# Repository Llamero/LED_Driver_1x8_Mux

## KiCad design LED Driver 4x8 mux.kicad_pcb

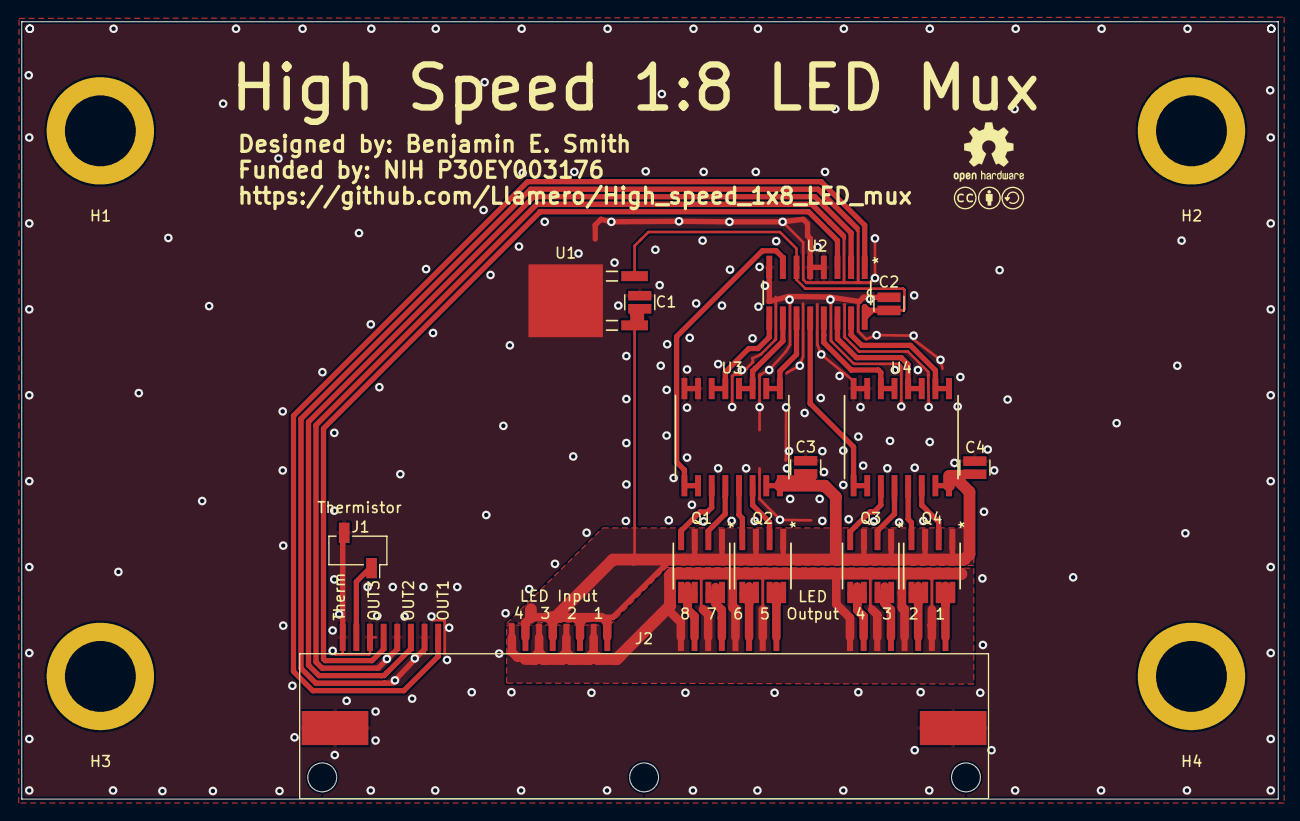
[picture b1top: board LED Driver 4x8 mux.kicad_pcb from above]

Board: 2 copper layers, 117.0 x 72.4 mm, 20 parts (0 on the bottom side), 32 nets.

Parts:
C1, C2, C3, C4: 2.2uF; 0508_Capacitor
H1, H2, H3, H4: MountingHole; 14-20_standoff
J1: 2 pin header; PinSocket_1x02_P2.54mm_Vertical_SMD_Pin1Right
J2: 8P8C_Shielded_x4; RJ45_x4-RJSSE-5380-04
LOGO1: CC license; Creative_commons_license
LOGO3: OSHW Logo; OSHW-Logo2_7.3x6mm_SilkScreen
Q1, Q2, Q3, Q4: SO8_IRF9358TRPBF_INF; IRF9358TRPBF-2x_p-channel
U1: NCV7805BDTRKG; 12V-5V_lin_reg_NCV7805BDTRKG
U2: SN74LV138AT_D_16; SN74LV138ATD
U3, U4: SOIC16-W_MC_MCH; TC4468EOE

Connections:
/+5V: C2.2, U1.3, U2.6, U2.16
/Gate1: Q4.2, U4.14
/Gate2: Q4.4, U4.13
/Gate3: Q3.2, U4.12
/Gate4: Q3.4, U4.11
/Gate5: Q2.2, U3.14
/Gate6: Q2.4, U3.13
/Gate7: Q1.2, U3.12
/Gate8: Q1.4, U3.11
/IN1: U2.15, U4.1, U4.2
/IN2: U2.14, U4.3, U4.4
/IN3: U2.13, U4.5, U4.6
/IN4: U2.12, U4.9, U4.10
/IN5: U2.11, U3.1, U3.2
/IN6: U2.10, U3.3, U3.4
/IN7: U2.9, U3.5, U3.6
/IN8: U2.7, U3.9, U3.10
/LED1+: J2.1, Q4.7, Q4.8
/LED2+: J2.3, Q4.5, Q4.6
/LED3+: J2.5, Q3.7, Q3.8
/LED4+: J2.7, Q3.5, Q3.6
/LED5+: J2.9, Q2.7, Q2.8
/LED6+: J2.11, Q2.5, Q2.6
/LED7+: J2.13, Q1.7, Q1.8
/LED8+: J2.15, Q1.5, Q1.6
/LED+: C1.2, C3.2, C4.2, J2.17, J2.19, J2.21, J2.23, Q1.1, Q1.3, Q2.1, Q2.3, Q3.1, Q3.3, Q4.1, Q4.3, U1.1, U3.15, U3.16, U4.15, U4.16
/LED-: J2.2, J2.4, J2.6, J2.8, J2.10, J2.12, J2.14, J2.16, J2.18, J2.20, J2.22, J2.24
/OUT1: J2.25, U2.1
/OUT2: J2.27, U2.2
/OUT3: J2.29, U2.3
/Thermistor: J1.1, J2.31
GND: C1.1, C2.1, C3.1, C4.1, J1.2, J2.26, J2.28, J2.30, J2.32, J2.SH, U1.2, U2.4, U2.5, U2.8, U3.7, U3.8, U4.7, U4.8

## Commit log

2023-08-26 update PCB
2023-09-02 PCB draft finished
2023-09-02 Add thermistor breakout
2023-09-30 Capacitors positions optimized
2023-09-30 Board powered off LED river backup
2023-09-30 LED driver external power
2023-09-30 Use Vin through LDO for 5V - no ext. power
    This redesign uses an linear regulator to drop the Vin voltage to 5V. This will greatly reduce the noise on the board, as well as the part count and complexity.
2023-10-06 Change name
2023-10-06 Update naming on board

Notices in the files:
parts and their libraries:
Copyright 2016 Accelerated Designs. All rights reserved.
